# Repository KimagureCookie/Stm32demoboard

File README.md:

# Stm32demoboard
This is created with the help of KiCad design tutorial video by Phil's Lab.

It was an amazing video to get started with KiCad and PCB designing.
The thing, I would never forgot is that its extremly difficult to handsolder 0402 😅.

This is a simple board with  UART,SPI and I2C interface.

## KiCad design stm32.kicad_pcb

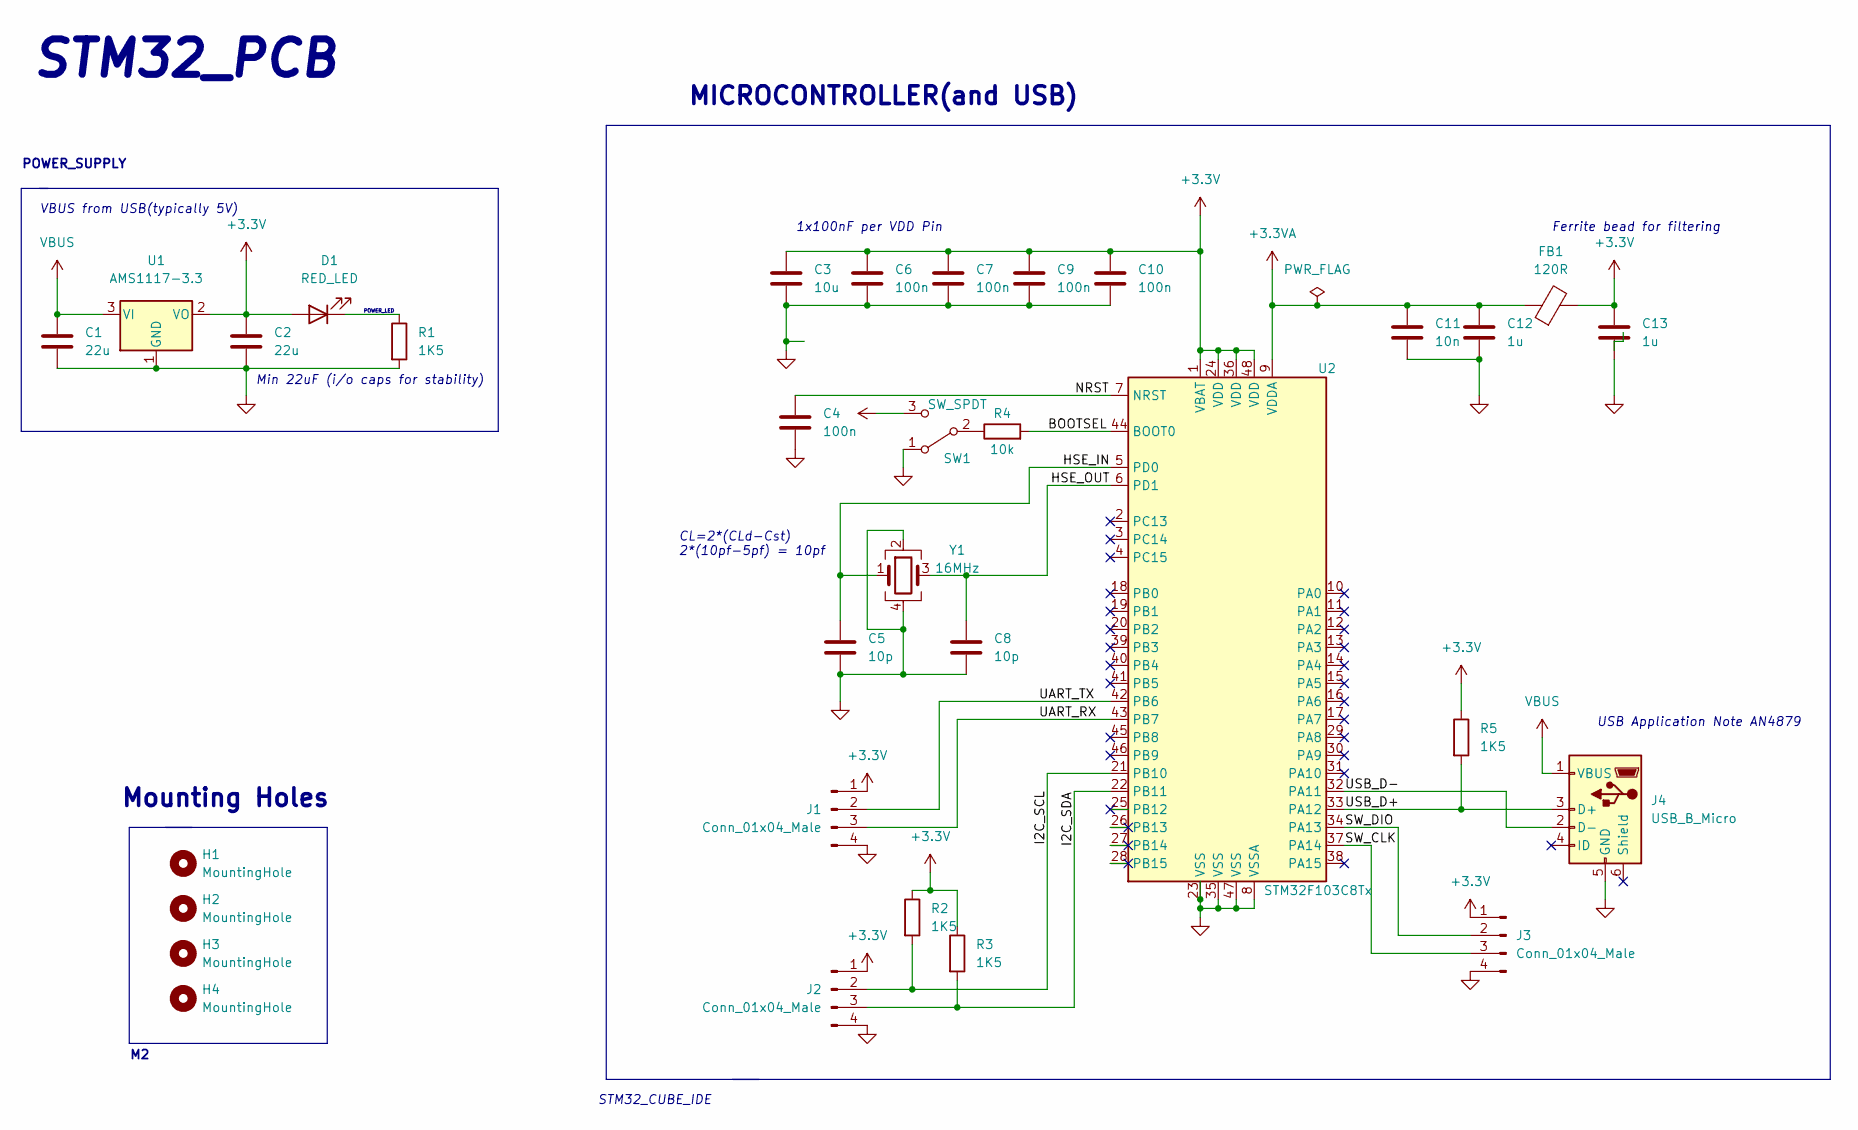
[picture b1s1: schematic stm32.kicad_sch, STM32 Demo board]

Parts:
C1, C2: 22u; C_0805_2012Metric_Pad1.18x1.45mm_HandSolder
C3: 10u; C_0603_1608Metric_Pad1.08x0.95mm_HandSolder
C4: 100n; C_0603_1608Metric_Pad1.08x0.95mm_HandSolder
C5, C8: 10p; C_0402_1005Metric_Pad0.74x0.62mm_HandSolder
C6, C7, C9, C10: 100n; C_0402_1005Metric_Pad0.74x0.62mm_HandSolder
C11: 10n; C_0402_1005Metric_Pad0.74x0.62mm_HandSolder
C12, C13: 1u; C_0402_1005Metric_Pad0.74x0.62mm_HandSolder
D1: RED_LED; LED_0603_1608Metric_Pad1.05x0.95mm_HandSolder
FB1: 120R; L_0805_2012Metric_Pad1.15x1.40mm_HandSolder
H1, H2, H3, H4: MountingHole; MountingHole_2.2mm_M2
J1, J2, J3: Conn_01x04_Male; PinHeader_1x04_P2.54mm_Vertical
J4: USB_B_Micro; USB_Micro-B_Wuerth_629105150521
R1, R5: 1K5; R_0402_1005Metric_Pad0.72x0.64mm_HandSolder
R2, R3: 1K5; R_0603_1608Metric_Pad0.98x0.95mm_HandSolder
R4: 10k; R_0402_1005Metric_Pad0.72x0.64mm_HandSolder
SW1: SW_SPDT; SW_SPDT_PCM12
U1: AMS1117-3.3; SOT-223-3_TabPin2
U2: STM32F103C8Tx; LQFP-48_7x7mm_P0.5mm
Y1: 16MHz; Crystal_SMD_3225-4Pin_3.2x2.5mm_HandSoldering

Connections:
+3.3V: C2.1, C3.1, C6.1, C7.1, C9.1, C10.1, C13.1, D1.2 (A), FB1.2, J1.1, J2.1, J3.1, R2.1, R3.1, R5.1, SW1.3 (C), U1.2 (VO), U2.1 (VBAT), U2.24 (VDD), U2.36 (VDD), U2.48 (VDD)
+3.3VA: C11.1, C12.1, FB1.1, U2.9 (VDDA)
/BOOTSEL: R4.2, U2.44 (BOOT0)
/HSE_IN: C5.1, U2.5 (PD0), Y1.1
/HSE_OUT: C8.1, U2.6 (PD1), Y1.3
/I2C_SCL: J2.2, R2.2, U2.21 (PB10)
/I2C_SDA: J2.3, R3.2, U2.22 (PB11)
/NRST: C4.1, U2.7 (NRST)
/SW_CLK: J3.3, U2.37 (PA14)
/SW_DIO: J3.2, U2.34 (PA13)
/UART_RX: J1.3, U2.43 (PB7)
/UART_TX: J1.2, U2.42 (PB6)
/USB_D+: J4.3 (D+), R5.2, U2.33 (PA12)
/USB_D-: J4.2 (D-), U2.32 (PA11)
GND: C1.2, C2.2, C3.2, C4.2, C5.2, C6.2, C7.2, C8.2, C9.2, C10.2, C11.2, C12.2, C13.2, J1.4, J2.4, J3.4, J4.5 (GND), R1.2, SW1.1 (A), U1.1 (GND), U2.8 (VSSA), U2.23 (VSS), U2.35 (VSS), U2.47 (VSS), Y1.2, Y1.4
unnamed: D1.1 (K), R1.1
unnamed: R4.1, SW1.2 (B)
VBUS: C1.1, J4.1 (VBUS), U1.3 (VI)

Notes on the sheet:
CL=2*(CLd-Cst) 2*(10pf-5pf) = 10pf
VBUS from USB(typically 5V)
MICROCONTROLLER(and USB)
Ferrite bead for filtering
Mounting Holes
POWER_SUPPLY
STM32_CUBE_IDE
USB Application Note AN4879
1x100nF per VDD Pin
POWER_LED
Min 22uF (i/o caps for stability)
STM32_PCB

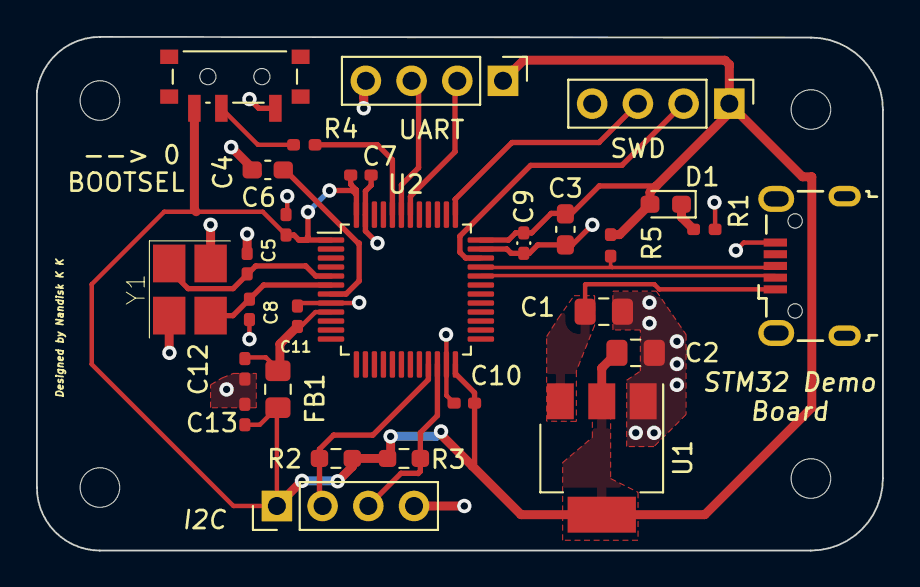
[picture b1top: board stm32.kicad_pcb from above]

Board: 2 copper layers, 47.0 x 28.5 mm, 32 parts (0 on the bottom side), 18 nets.

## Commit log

2023-05-07 Stm32_board_added
2023-05-07 pic added
